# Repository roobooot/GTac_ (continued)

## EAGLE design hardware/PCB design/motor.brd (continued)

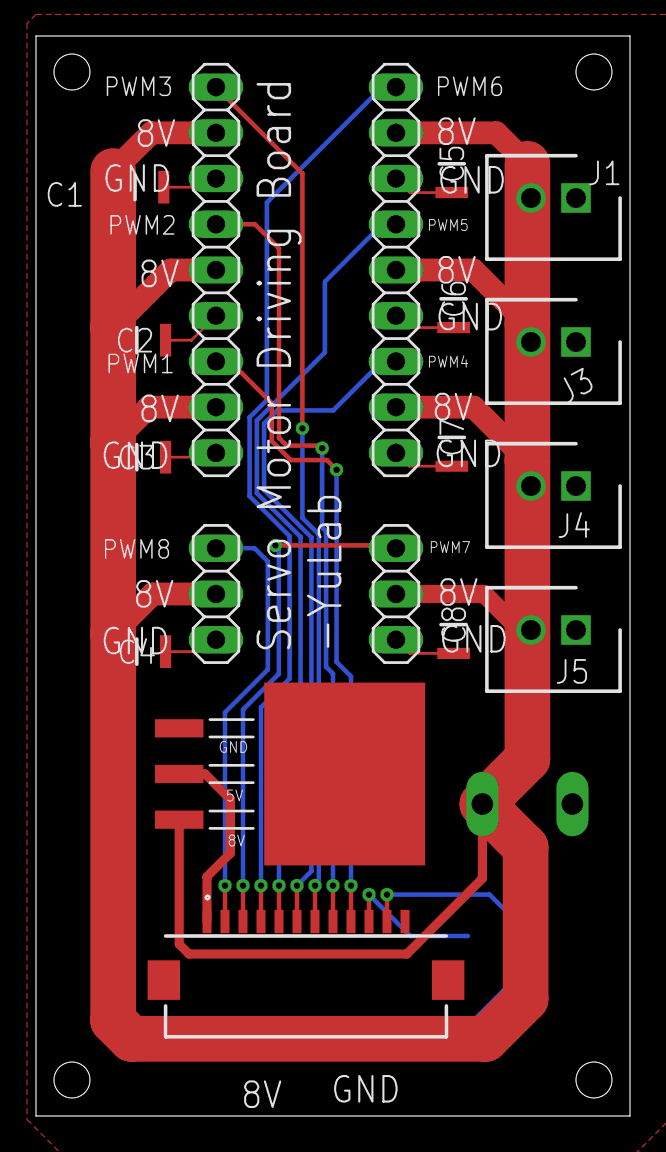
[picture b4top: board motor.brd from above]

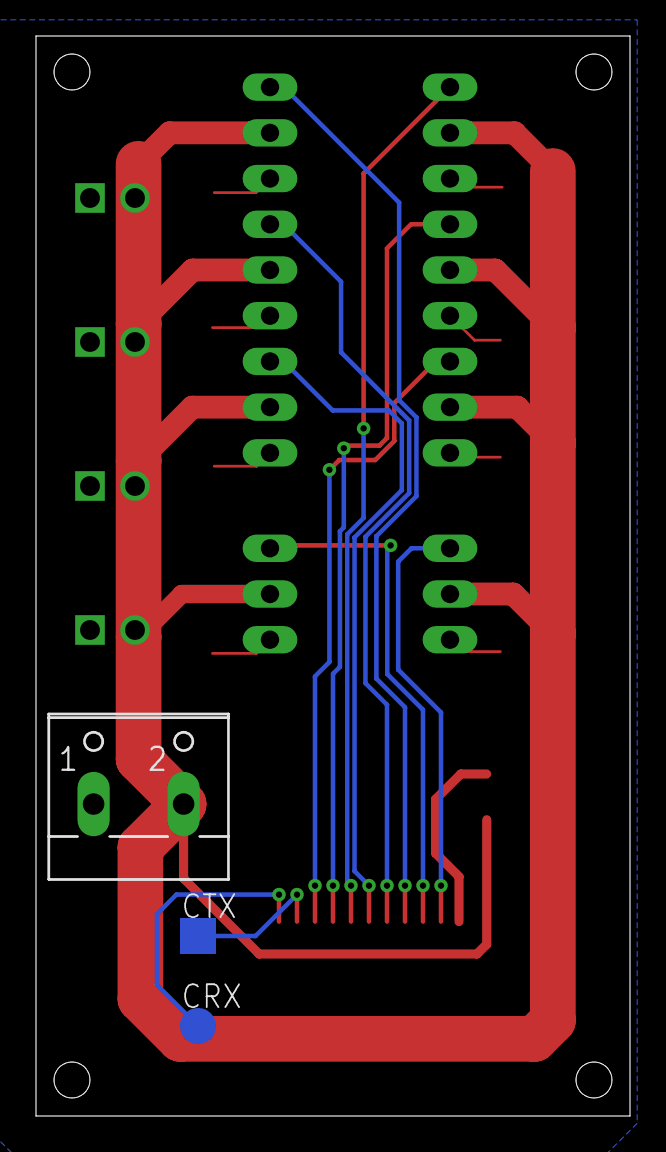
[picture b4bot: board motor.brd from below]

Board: 2 copper layers, 33.0 x 60.0 mm, 21 parts (3 on the bottom side), 13 nets.

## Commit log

2022-01-29 init the files
2022-01-29 update the files
2022-01-29 Set theme jekyll-theme-cayman
2022-02-11 organized the files
2022-02-28 update code of GTac-Gripper
2022-03-01 Set theme jekyll-theme-hacker
2022-03-01 add link
2022-03-01 add gif
2022-04-20 update for gtac sensor
2022-04-20 update readme for GTac sensor
2022-04-20 update sensor readme
2022-04-20 update default save path
2022-04-21 update files elect
2022-04-25 Updata the readme for data using
2022-06-01 recover
2022-08-12 update gtac hand
2022-08-17 update links
2022-09-27 update gp2
2022-09-27 update img size
2022-09-27 update gp2 img
2022-09-27 update gp2 img2
2022-09-27 update gp2 text
2022-09-27 update gp2 txt
2022-09-29 update swab test
2022-09-29 update swab
2022-09-29 udpate swab
2022-09-29 update wabs
2022-09-29 udpate sadw
2022-12-02 Add initial python package
2022-12-05 Add interface for a single sensor
